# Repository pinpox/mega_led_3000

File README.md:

# mega_led_3000

Remote + Controller for a RGB LED light strip.

The project consists of two parts: a base unit that is connected to the LED-strip and a remote control unit. Both are build using Arduinos and some other parts (see below) and communnicate over 2.4 GHz signals.

The sourcecode is separted in the respective folders so that it can be build and uploaded using the inotool for arduino (http://inotool.org/quickstart)

For the 2.4GHz communication the RF24 library is used (https://github.com/nRF24/RF24).

## Schematic

## Partlist

#### Base unit
- Arduino Uno
- nRF24L01 2.4 GHz transciever
- 3x Resistor 440 Ohm
- 3x TIP120 Transistor

#### Remote
- Arduino Micro
- nRF24L01 2.4 GHz transciever
- 3x EXP-R05-031 RGB-illuminated rotatory encoders

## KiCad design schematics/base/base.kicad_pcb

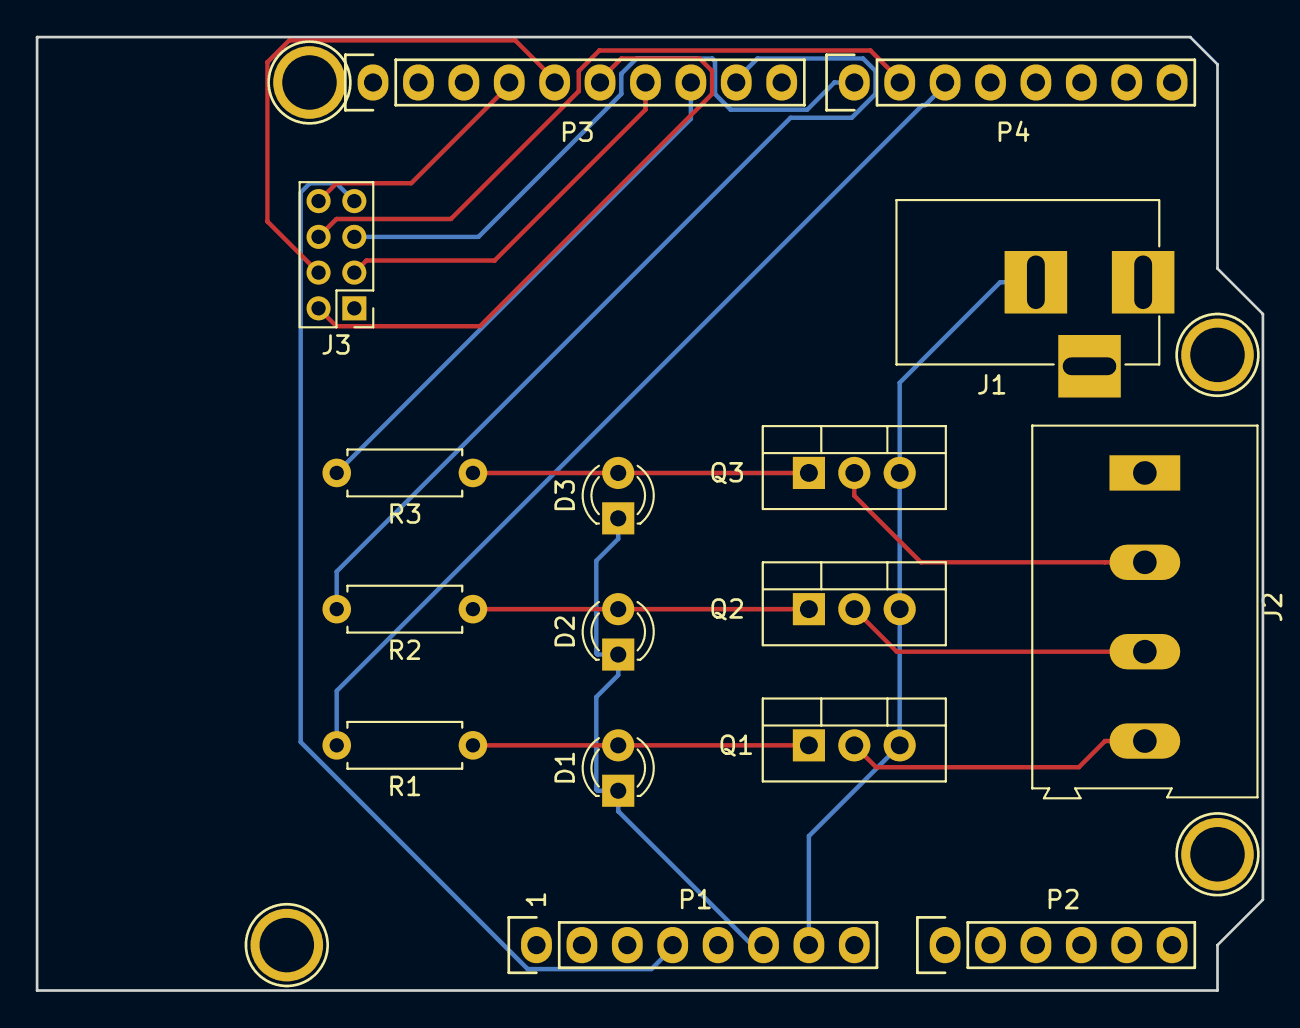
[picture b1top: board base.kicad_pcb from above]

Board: 2 copper layers, 68.6 x 53.3 mm, 20 parts (0 on the bottom side), 18 nets.

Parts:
D1, D2, D3: LED; LED_D3.0mm
J1: BARREL_JACK
J2: CONN_01X04_FEMALE; AK300-4
J3: CONN_02X04; Pin_Header_Straight_2x04_Pitch2.00mm
P1: Power; Socket_Strip_Arduino_1x08
P2: Analog; Socket_Strip_Arduino_1x06
P3: Digital; Socket_Strip_Arduino_1x10
P4: Digital; Socket_Strip_Arduino_1x08
P5, P6, P7, P8: CONN_01X01; Arduino_1pin
Q1, Q2, Q3: TIP120; TO-220_Vertical
R1, R2, R3: R; R_Axial_DIN0207_L6.3mm_D2.5mm_P7.62mm_Horizontal

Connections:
/5(**): P4.3, R1.2
/6(**): J3.6, P4.2
/7: J3.5, P4.1
/9(**): P3.9, R2.2
/10(**/SS): P3.8, R3.2
/11(**/MOSI): J3.3, P3.7
/12(MISO): J3.2, P3.6
/13(SCK): J3.4, P3.5
GND: D1.1, D2.1, D3.1, J1.2, P1.6, P1.7, Q1.3, Q2.3, Q3.3
unnamed: J1.1, J2.1
unnamed: J2.2, Q3.2
unnamed: J2.3, Q2.2
unnamed: J2.4, Q1.2
unnamed: J3.7, P1.4
unnamed: J3.8, P3.4
unnamed: Q1.1, R1.1
unnamed: Q2.1, R2.1
unnamed: Q3.1, R3.1

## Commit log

2017-04-12 base structure for receiver
2017-04-12 docs
2017-04-12 ignore
2017-04-12 added func for encoder turn recognition
2017-04-12 added ano files to gitignore
2017-04-12 added working examples of wireless communication
2017-04-12 Added wiring diagrams for base and receiver
2017-04-13 added necessary libraries to compile sketches
2017-04-13 added build configurations
2017-04-13 moved examples to proper files
2017-04-13 Communication works, strip color can be set via 6 buttons for rgb up and down"
2017-04-14 added kicad projects for schematics using arduino templates
2017-04-14 added first version of base pcb and schematic
2017-04-17 added schematic for base
2017-04-26 changed base to receive absolute valuesw
2017-04-26 remote sending abs values
2017-04-26 cleaned up base code
